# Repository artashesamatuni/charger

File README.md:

# Single-phase AC EVSE prototype

Engineering baseline for a European Mode 3 EV supply equipment prototype:

- 230 V AC, single phase
- 32 A maximum (7.4 kW nominal), configurable 6–32 A
- permanently attached cable with Type 2 vehicle connector (Case C)
- ESP32 controller with Wi-Fi
- IEC 61851 control pilot

Engineering documents:

- [System baseline](docs/system-baseline.md): external I/O, safety concept, self-tests, charging state machine, hardware architecture, and firmware partitioning.
- [System requirements](docs/system-requirements.md): traceable, verifiable product requirements.
- [Preliminary hazard analysis](docs/hazard-analysis.md): design FMEA and required independent safety paths.
- [Architecture and interface specification](docs/architecture-and-interfaces.md): frozen product options, subsystem partitioning, communications, UI, and schematic-sheet plan.
- [Thermal derating algorithm](docs/thermal-derating.md): sensor validation, current limiting, shutdown/recovery behavior, and environmental test matrix.\n- [Rev A controller schematic specification](hardware/rev-a/controller-schematic-spec.md): ESP32-S3, BRCS01C, watchdog, hardwired contactor inhibit, self-test, and KiCad sheet plan.\n- [Rev A preliminary BOM](hardware/rev-a/preliminary-bom.csv): selected, provisional, and open controller components.

> This repository is an engineering prototype, not certified equipment. Mains testing requires appropriate competence, isolation, protection, enclosure, and test equipment. Do not connect a vehicle or public supply until the safety circuits and fault responses have been independently reviewed and tested.

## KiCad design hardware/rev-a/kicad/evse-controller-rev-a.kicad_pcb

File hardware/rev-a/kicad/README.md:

# KiCad schematic — Rev A

## Open the schematic

Open `evse-controller-rev-a.sch` in KiCad 8 or 9. It is stored in the KiCad legacy schematic format so it remains human-reviewable in GitHub. KiCad will offer to convert it; save the converted result as `.kicad_sch`.

## Current content

- protected 24 V input;
- provisional 5.5 V, 5 V RDC and 3.3 V power stages;
- ESP32-S3-WROOM-1;
- BRCS01C-05-H1 connector;
- fail-safe pull-up interpretation for both trip outputs;
- hardware safety-latch functional block;
- TPS3430-Q1 watchdog functional block;
- Type 2 CP/PP connector;
- future contactor interface, with contactor and coil driver DNP.

## Verification status

The text structure is balanced and contains 16 component blocks and 52 wire records. KiCad and ERC were not available on the authoring host, so graphical import, symbol resolution and ERC are **not yet verified**.

Do not assign PCB footprints or order a PCB from this draft. Several complex devices are represented as named functional connector blocks while their exact implementation is refined in the adjacent sheet-definition documents.

## Required KiCad review

1. Open and convert the legacy file.
2. Confirm that `RF_Module:ESP32-S3-WROOM-1` resolves with the installed symbol library.
3. Inspect power pin visibility and pin mapping.
4. Replace each named functional connector block with the final manufacturer symbol.
5. Add no-connect flags intentionally.
6. Run ERC with custom safety rules.
7. Export PDF and visually inspect every net and junction.

The contactor will be added only after its exact model and coil interface are frozen.

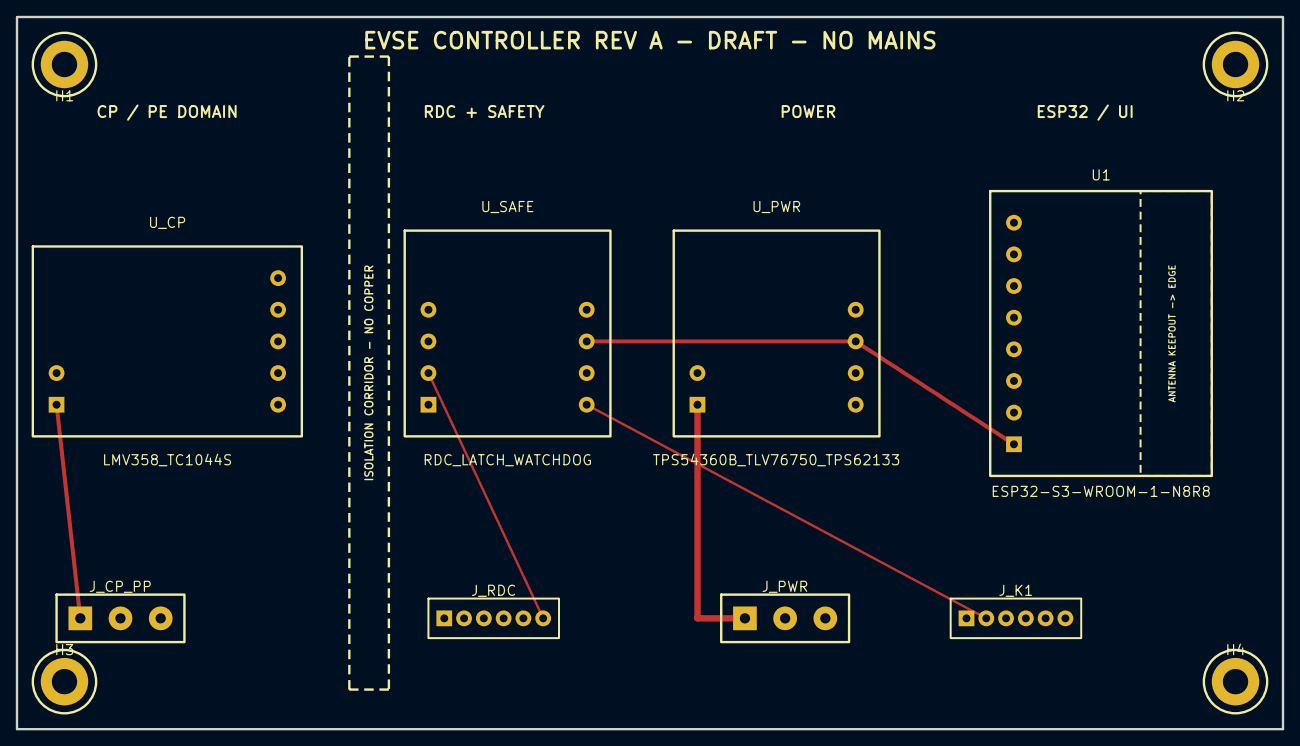
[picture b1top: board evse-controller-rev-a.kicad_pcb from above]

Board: 2 copper layers, 160.0 x 90.0 mm, 12 parts (0 on the bottom side), 17 nets.

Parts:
H1, H2, H3, H4: M3_Mount
J_CP_PP: Terminal_1x3_5.08
J_K1: JST_1x6
J_PWR: 24V_IN; Terminal_1x3_5.08
J_RDC: JST_1x6
U1: ESP32-S3-WROOM-1-N8R8; ESP32_S3_MODULE
U_CP: LMV358_TC1044S; CP_ANALOG_BLOCK
U_PWR: TPS54360B_TLV76750_TPS62133; POWER_BLOCK
U_SAFE: RDC_LATCH_WATCHDOG; SAFETY_BLOCK

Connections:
+3V3: U1.1, U_CP.5, U_PWR.5, U_SAFE.7
+5V_RDC: J_RDC.1, U_PWR.4
+24V_IN: J_PWR.1, U_PWR.1
+24V_PROT: J_K1.1, U_CP.7, U_PWR.2
CP: J_CP_PP.1, U_CP.1
CP_PWM: U1.3, U_CP.3
CP_SENSE: U1.4, U_CP.4
GND_SELV: J_K1.6, J_PWR.2, J_RDC.3, U1.2, U_CP.6, U_PWR.6, U_SAFE.8
K1_AUX_L: J_K1.3, U1.7
K1_AUX_N: J_K1.4, U1.8
K1_HW_ENABLE: J_K1.2, U_SAFE.5
PE: J_CP_PP.3, J_PWR.3
PP: J_CP_PP.2, U_CP.2
RDC_ACDC_RAW: J_RDC.2, U_SAFE.1
RDC_CAL: J_RDC.4, U1.6, U_SAFE.4
RDC_DC_RAW: J_RDC.6, U_SAFE.2
RDC_TEST: J_RDC.5, U1.5, U_SAFE.3
